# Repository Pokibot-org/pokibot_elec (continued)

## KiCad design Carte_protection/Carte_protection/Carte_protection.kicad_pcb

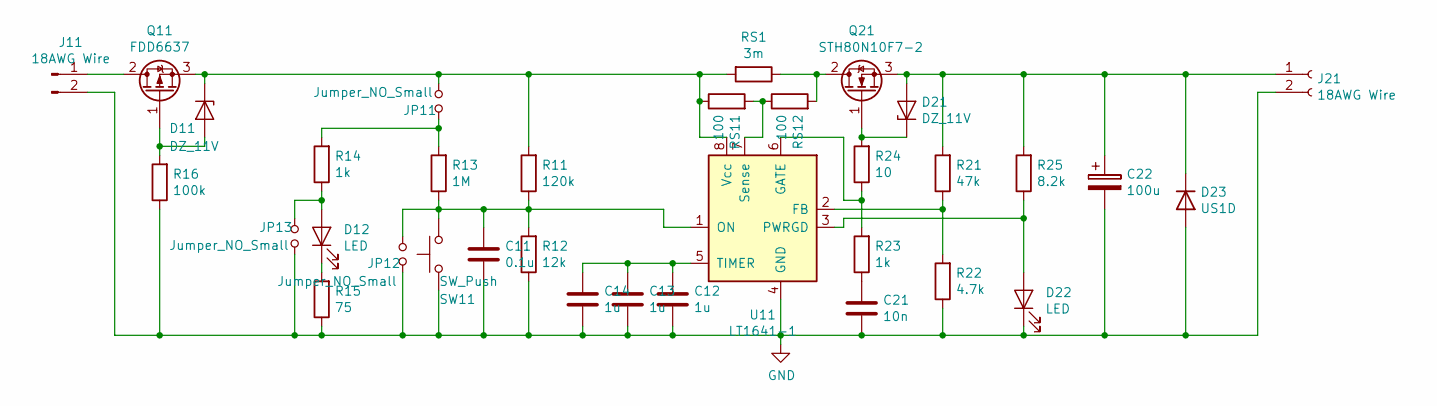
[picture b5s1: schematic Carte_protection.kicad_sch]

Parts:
C11: 0.1u; C_1206_3216Metric
C12, C13, C14: 1u; C_1206_3216Metric
C21: 10n; C_0805_2012Metric
C22: 100u; CP_Elec_6.3x5.8
D11, D21: DZ_11V; D_SOD-123
D12, D22: LED; LED_0805_2012Metric
D23: US1D; D_SMA
J11, J21: 18AWG Wire; Molex_KK-396_A-41791-0002_1x02_P3.96mm_Vertical
JP11, JP12, JP13: Jumper_NO_Small; Molex_KK-254_AE-6410-02A_1x02_P2.54mm_Vertical
Q11: FDD6637; TO-252-2
Q21: STH80N10F7-2; TO-263-2
R11: 120k; R_0805_2012Metric
R12: 12k; R_0805_2012Metric
R13: 1M; R_0805_2012Metric
R14, R23: 1k; R_0805_2012Metric
R15: 75; R_0805_2012Metric
R16: 100k; R_0805_2012Metric
R21: 47k; R_0805_2012Metric
R22: 4.7k; R_0805_2012Metric
R24: 10; R_1206_3216Metric
R25: 8.2k; R_0805_2012Metric
RS1: 3m; R_2010_5025Metric
RS11, RS12: 100; R_0805_2012Metric
SW11: SW_Push; SW_Push_1P1T_NO_6x6mm_H9.5mm
U11: LT1641-1; SOIC-8_3.9x4.9mm_P1.27mm

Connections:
GND: C11.2, C12.2, C13.2, C14.2, C21.2, C22.2, D22.1 (K), D23.2 (A), J11.2, J21.2, JP12.2, JP13.2, R12.1, R15.1, R16.1, R22.1, SW11.1, U11.4 (GND)
unnamed: C11.1, JP12.1, R11.1, R12.2, R13.1, SW11.2, U11.1 (ON)
unnamed: C12.1, C13.1, C14.1, U11.5 (TIMER)
unnamed: C21.1, R23.1
unnamed: C22.1, D21.2 (A), D23.1 (K), J21.1, Q21.3 (S), R21.2, R25.2
unnamed: D11.1 (K), JP11.2, Q11.3 (S), R11.2, RS1.2, RS11.1, U11.8 (Vcc)
unnamed: D11.2 (A), Q11.1 (G), R16.2
unnamed: D12.1 (K), R15.2
unnamed: D12.2 (A), JP13.1, R14.1
unnamed: D21.1 (K), Q21.1 (G), R24.2
unnamed: D22.2 (A), R25.1, U11.3 (PWRGD)
unnamed: J11.1, Q11.2 (D)
unnamed: JP11.1, R13.2, R14.2
unnamed: Q21.2 (D), RS1.1, RS12.2
unnamed: R21.1, R22.2, U11.2 (FB)
unnamed: R23.2, R24.1, U11.6 (GATE)
unnamed: RS11.2, RS12.1, U11.7 (Sense)

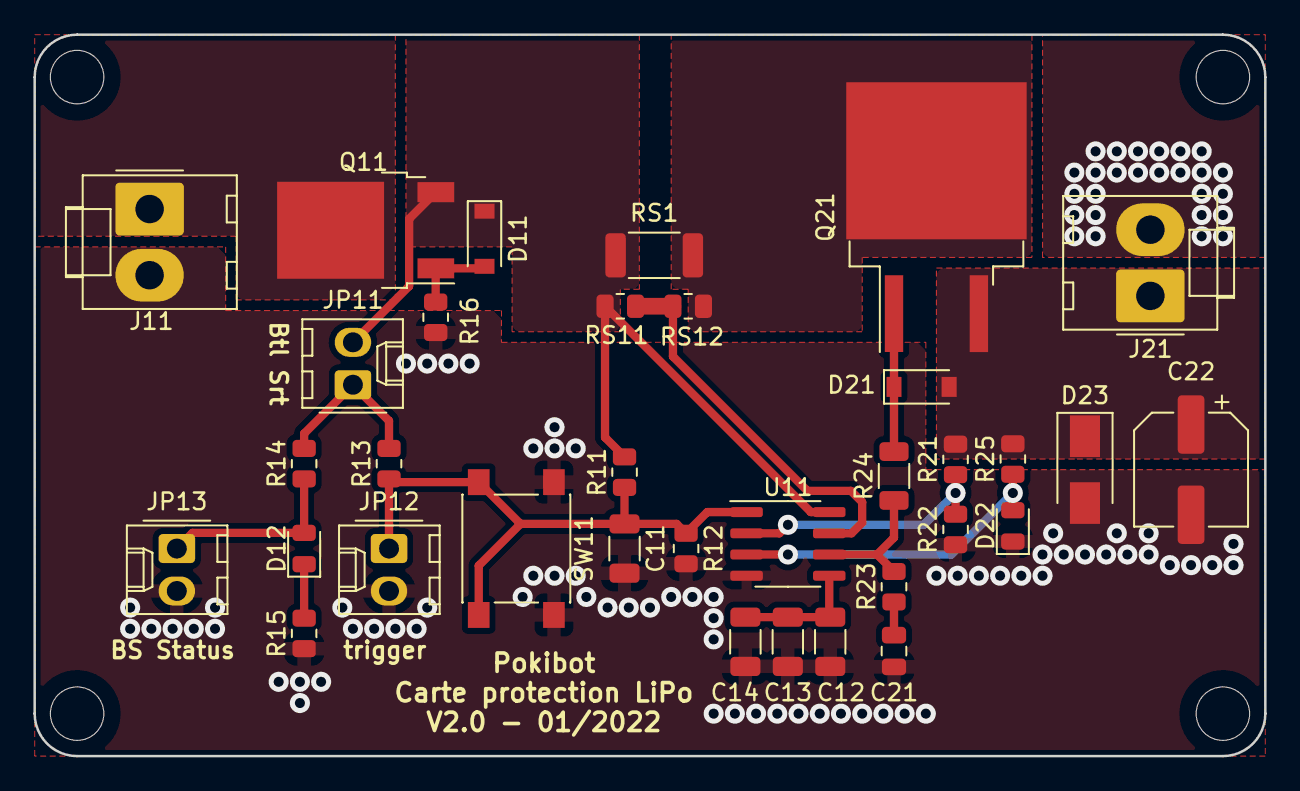
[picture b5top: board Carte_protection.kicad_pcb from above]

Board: 2 copper layers, 73.7 x 43.2 mm, 34 parts (0 on the bottom side), 17 nets.

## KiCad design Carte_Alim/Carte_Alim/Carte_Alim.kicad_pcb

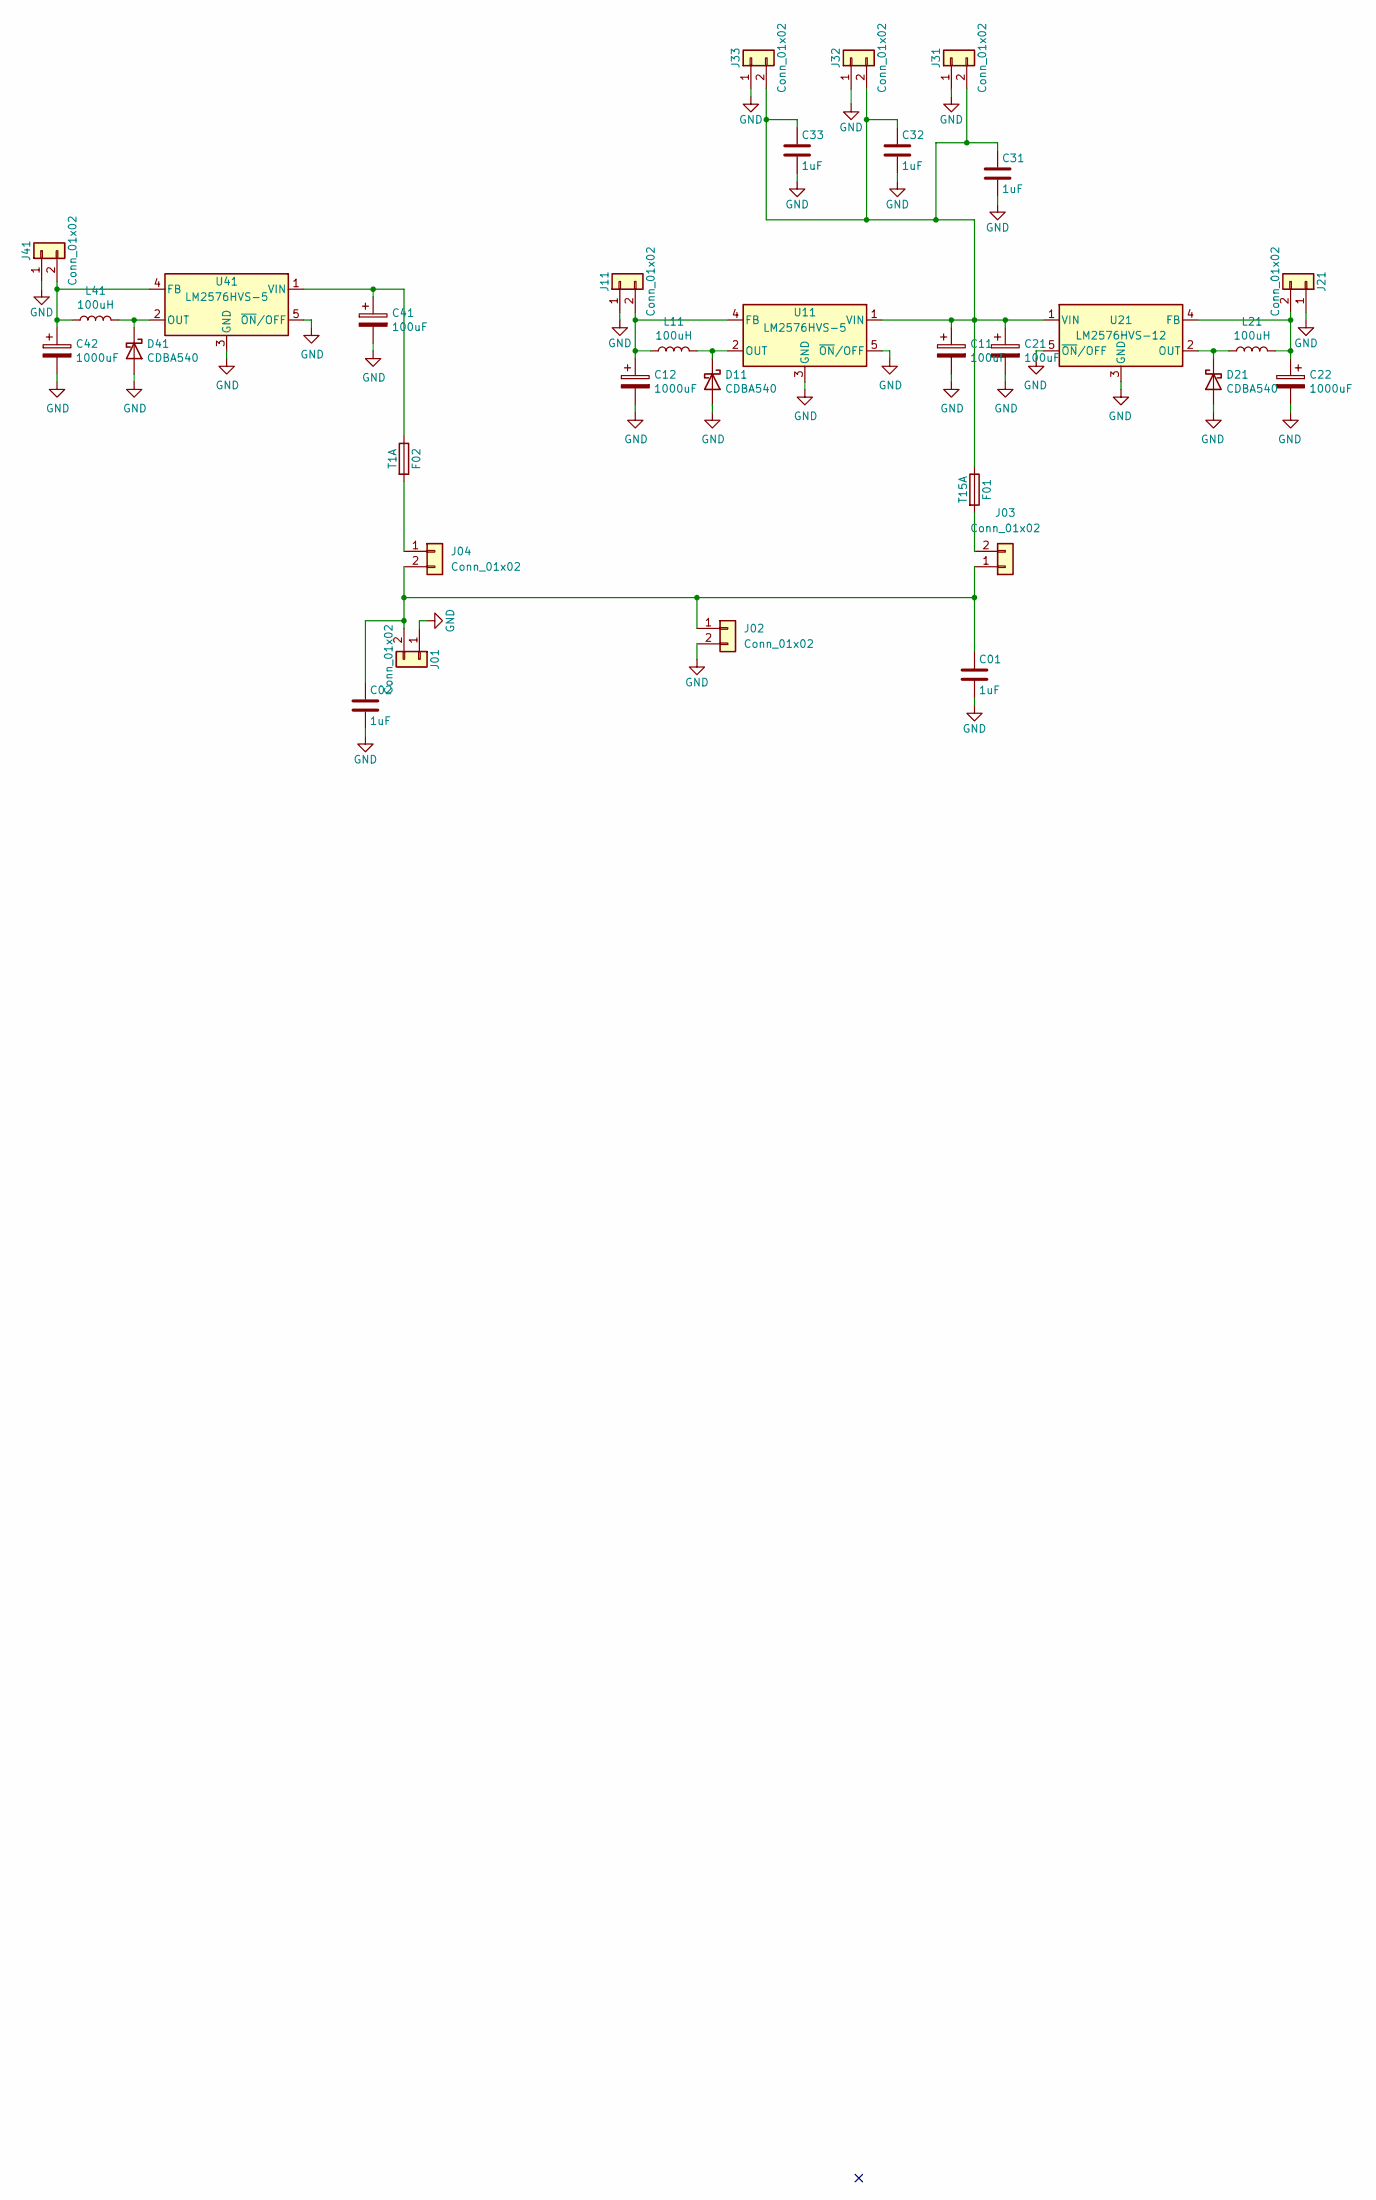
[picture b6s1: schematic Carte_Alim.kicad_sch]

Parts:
C01, C02, C31, C32, C33: 1uF; C_1206_3216Metric_Pad1.33x1.80mm_HandSolder
C11, C21, C41: 100uF; CP_Elec_6.3x3.9
C12, C22, C42: 1000uF; CP_Radial_D10.0mm_P5.00mm
D11, D21, D41: CDBA540; D_SMA
F01: T15A; Fuseholder_Littelfuse_100_series_5x20mm
F02: T1A; Fuseholder_Littelfuse_100_series_5x20mm
J01, J03, J04, J11, J21, J31, J32, J33, J41: Conn_01x02; Molex_KK-396_A-41791-0002_1x02_P3.96mm_Vertical
J02: Conn_01x02; Molex_KK-254_AE-6410-02A_1x02_P2.54mm_Vertical
L11, L21, L41: 100uH; L_Wuerth_WE-PD-Typ-LS
U11, U41: LM2576HVS-5; TO-220F-5_Horizontal_TabDown
U21: LM2576HVS-12; TO-220F-5_Horizontal_TabDown

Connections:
GND: C01.2, C02.2, C11.2, C12.2, C21.2, C22.2, C31.2, C32.2, C33.2, C41.2, C42.2, D11.2 (A), D21.2 (A), D41.2 (A), J01.1, J02.2, J11.1, J21.1, J31.1, J32.1, J33.1, J41.1, U11.3 (GND), U11.5 (~ON/OFF), U21.3 (GND), U21.5 (~ON/OFF), U41.3 (GND), U41.5 (~ON/OFF)
unnamed: C01.1, C02.1, J01.2, J02.1, J03.1, J04.2
unnamed: C11.1, C21.1, C31.1, C32.1, C33.1, F01.1, J31.2, J32.2, J33.2, U11.1 (VIN), U21.1 (VIN)
unnamed: C12.1, J11.2, L11.1, U11.4 (FB)
unnamed: C22.1, J21.2, L21.1, U21.4 (FB)
unnamed: C41.1, F02.1, U41.1 (VIN)
unnamed: C42.1, J41.2, L41.1, U41.4 (FB)
unnamed: D11.1 (K), L11.2, U11.2 (OUT)
unnamed: D21.1 (K), L21.2, U21.2 (OUT)
unnamed: D41.1 (K), L41.2, U41.2 (OUT)
unnamed: F01.2, J03.2
unnamed: F02.2, J04.1

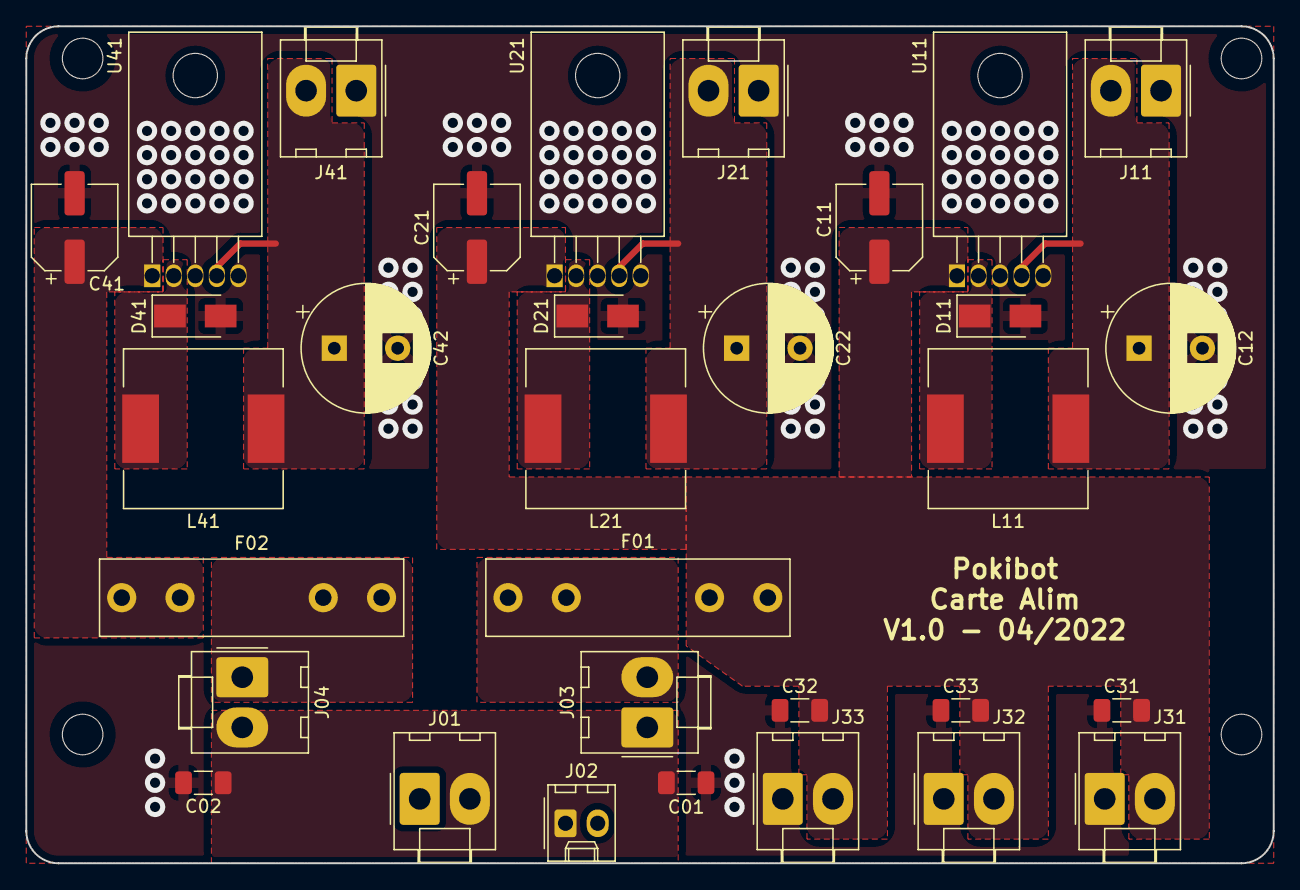
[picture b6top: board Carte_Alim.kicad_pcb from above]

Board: 2 copper layers, 98.4 x 66.0 mm, 32 parts (0 on the bottom side), 12 nets.

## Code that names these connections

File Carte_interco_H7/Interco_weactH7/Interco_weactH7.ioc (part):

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Mcu.Name=STM32H743VITx
Mcu.Package=LQFP100
Mcu.UserName=STM32H743VITx
PA0.Signal=S_TIM5_CH1
PA1.Signal=S_TIM5_CH2
PA11.Mode=Asynchronous
PA11.Signal=UART4_RX
PA12.Mode=Asynchronous
PA12.Signal=UART4_TX
PA13\ (JTMS/SWDIO).Signal=DEBUG_JTMS-SWDIO
PA14\ (JTCK/SWCLK).Signal=DEBUG_JTCK-SWCLK
PA15\ (JTDI).Signal=SPI3_NSS
PA2.Mode=Asynchronous
PA2.Signal=USART2_TX
PA3.Mode=Asynchronous
PA3.Signal=USART2_RX
PA4.Signal=GPIO_Output
PA5.Signal=S_TIM2_CH1_ETR
PB10.Mode=Asynchronous
PB10.Signal=USART3_TX
PB11.Mode=Asynchronous
PB11.Signal=USART3_RX
PB12.Mode=Asynchronous
PB12.Signal=UART5_RX
PB13.Mode=Asynchronous
PB13.Signal=UART5_TX
PB14.Mode=Asynchronous
PB14.Signal=USART1_TX
PB15.Mode=Asynchronous
PB15.Signal=USART1_RX
PB4\ (NJTRST).Signal=S_TIM3_CH1
PB5.Signal=S_TIM3_CH2
PC10.Mode=Full_Duplex_Master
PC10.Signal=SPI3_SCK
PC11.Mode=Full_Duplex_Master
PC11.Signal=SPI3_MISO
PC12.Mode=Full_Duplex_Master
PC12.Signal=SPI3_MOSI
PC6.Mode=Asynchronous
PC6.Signal=USART6_TX
PC7.Mode=Asynchronous
PC7.Signal=USART6_RX
PC8.Signal=S_TIM3_CH3
PD12.Signal=S_TIM4_CH1
PD13.Signal=S_TIM4_CH2
PD14.Signal=S_TIM4_CH3
PD15.Signal=S_TIM4_CH4
PE0.Mode=Asynchronous
PE0.Signal=UART8_RX
PE1.Mode=Asynchronous
PE1.Signal=UART8_TX
PE11.Signal=S_TIM1_CH2
PE13.Signal=S_TIM1_CH3
PE14.Signal=S_TIM1_CH4
PE7.Mode=Asynchronous
PE7.Signal=UART7_RX
PE8.Mode=Asynchronous
PE8.Signal=UART7_TX
PE9.Signal=S_TIM1_CH1
RCC.SYSCLKFreq_VALUE=64000000
board=custom

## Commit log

2022-05-09 Here we go again...
2025-02-26 ignore backups directory
2025-02-26 added motor control board, WIP
2025-03-02 updated motor PCB
2025-03-03 include lockfiles in gitignore
2025-03-03 debug led added. Modified power connector
2025-03-09 changed pwr connector
2025-03-09 update gerber archive file
2025-03-09 all board angles are now round like a bull testicule, to please mat3ck
2025-03-09 powki board added
2025-03-09 schematic+gerber update
2025-03-14 add BOM
2025-03-20 update motor board values
2025-03-21 fuck. Fuck fuck. Fuck Fuck Fuck. FUUCKING FUCK
2025-03-30 AAAAAAAAAAAAAAAA
2025-03-30 Routage v1.1
2025-03-30 add masks
2025-03-31 smol changes + export gerber
2025-04-15 bin for stlink added
2025-04-24 WIK main componenet ok. bck before adding extra I/O
2025-04-27 WIP. layout ok
2025-04-27 ready for check
2025-04-28 Schematics ok
2025-04-28 pins in conflict rerouted
2025-04-29 P1 connector was backward
2025-05-01 send PCB
